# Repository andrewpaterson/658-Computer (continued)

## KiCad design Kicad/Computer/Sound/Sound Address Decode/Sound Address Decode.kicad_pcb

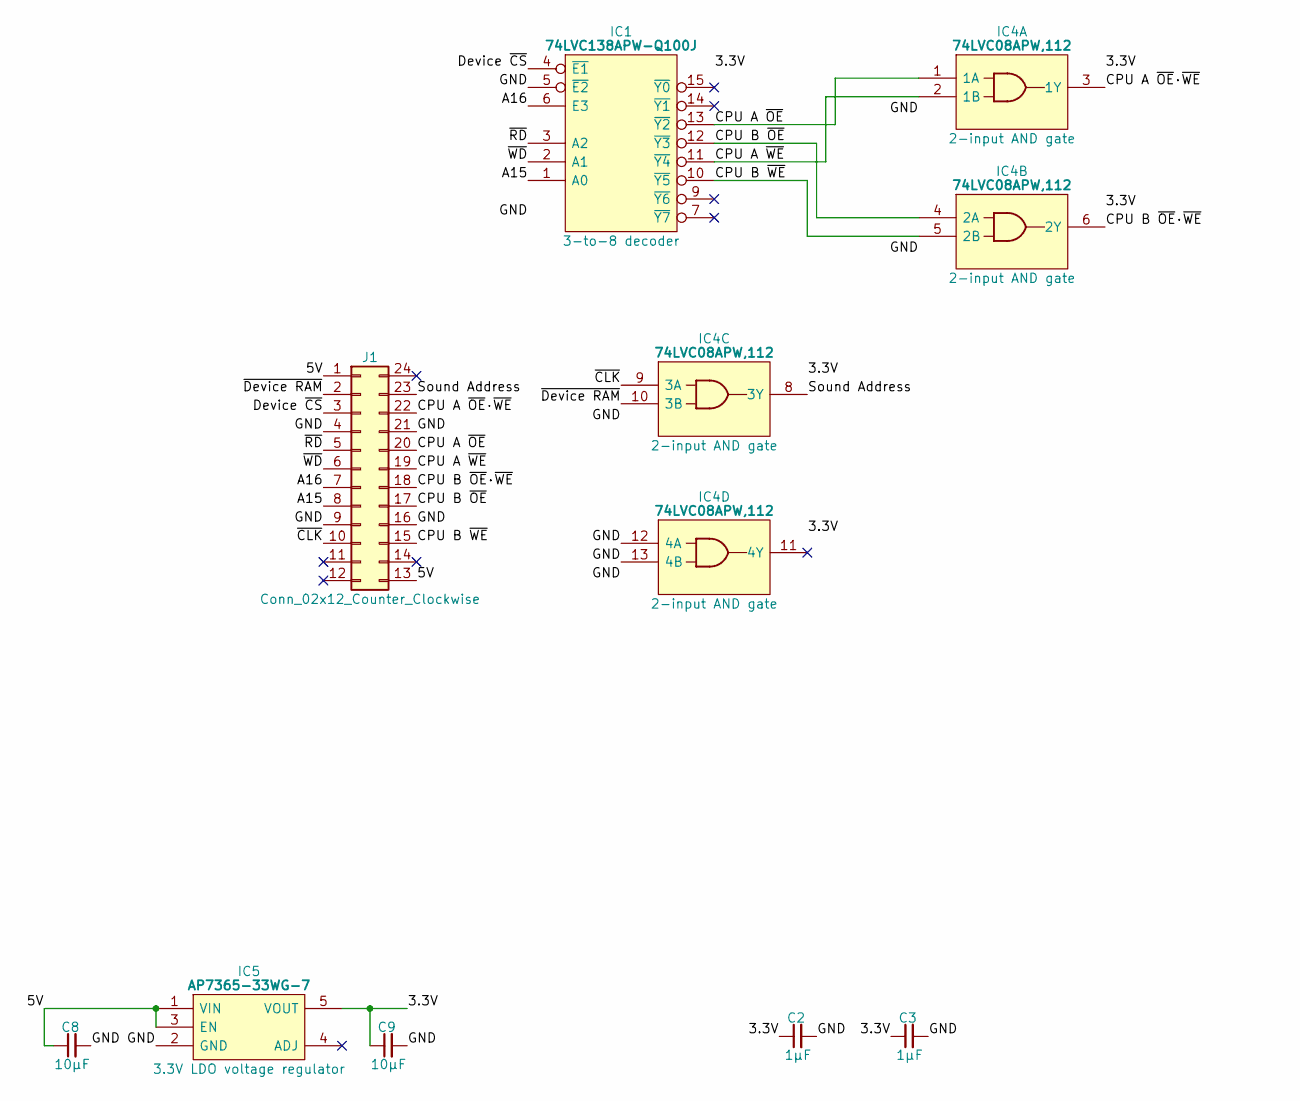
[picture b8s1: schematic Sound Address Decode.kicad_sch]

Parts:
C2, C3: 1μF; C_0805
C8, C9: 10µF; C_0805
IC1: 74LVC138APW-Q100J; SOP65P640X110-16N; Mouser Part Number 771-74LVC138APWQ100J
IC4: 74LVC08APW,112; SOP65P640X110-14N; Manufacturer_Part_Number 74LVC08APW,112; Mouser Part Number 771-74LVC08APW
IC5: AP7365-33WG-7; SOT95P285X130-5N; Manufacturer_Part_Number AP7365-33WG-7; Mouser Part Number 621-AP7365-33WG-7
J1: Conn_02x12_Counter_Clockwise; DIP-24_Board_W15.24mm

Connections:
/3.3V: C2.1, C3.1, C9.1, IC1.16 (3V), IC4.14 (3V), IC5.5 (VOUT)
/5V: C8.1, IC5.1 (VIN), IC5.3 (EN), J1.1, J1.13
/A15: IC1.1 (A0), J1.8
/A16: IC1.6 (E3), J1.7
/CPU A ~OE: IC1.13 (~Y2), IC4.1 (1A), J1.20
/CPU A ~OE·~WE: IC4.3 (1Y), J1.22
/CPU A ~WE: IC1.11 (~Y4), IC4.2 (1B), J1.19
/CPU B ~OE: IC1.12 (~Y3), IC4.4 (2A), J1.17
/CPU B ~OE·~WE: IC4.6 (2Y), J1.18
/CPU B ~WE: IC1.10 (~Y5), IC4.5 (2B), J1.15
/Device ~CS: IC1.4 (~E1), J1.3
/GND: C2.2, C3.2, C8.2, C9.2, IC1.5 (~E2), IC1.8 (GND), IC4.7 (GND), IC4.12 (4A), IC4.13 (4B), IC5.2 (GND), J1.4, J1.9, J1.16, J1.21
/Sound Address: IC4.8 (3Y), J1.23
/~CLK: IC4.9 (3A), J1.10
/~Device RAM: IC4.10 (3B), J1.2
/~RD: IC1.3 (A2), J1.5
/~WD: IC1.2 (A1), J1.6

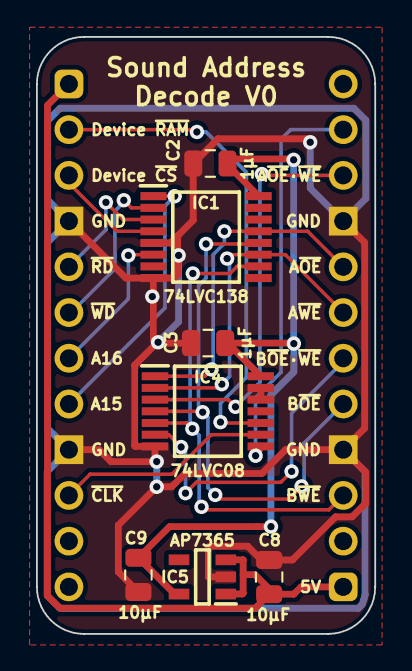
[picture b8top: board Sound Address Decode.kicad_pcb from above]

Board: 2 copper layers, 18.8 x 33.2 mm, 8 parts (0 on the bottom side), 17 nets.
